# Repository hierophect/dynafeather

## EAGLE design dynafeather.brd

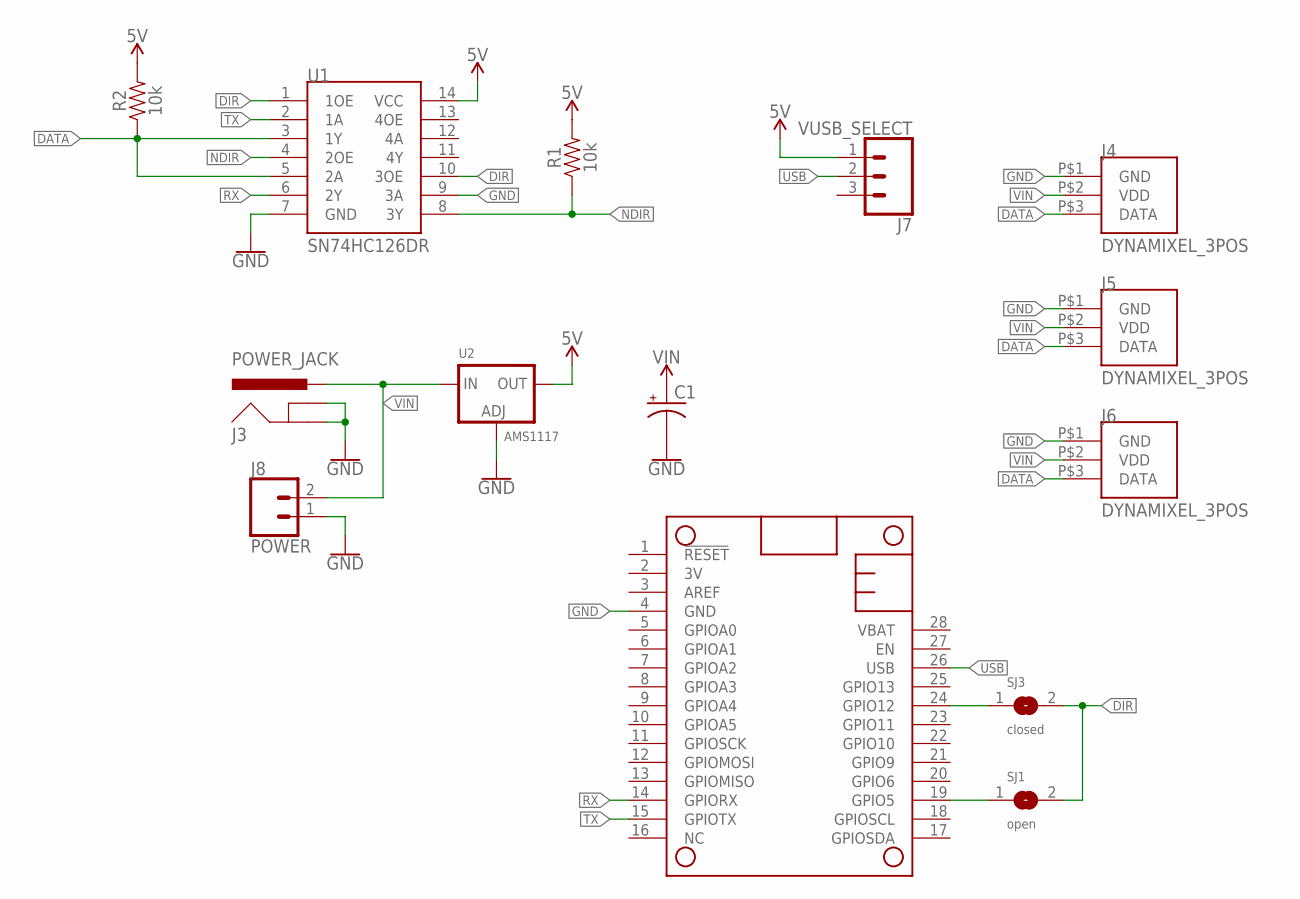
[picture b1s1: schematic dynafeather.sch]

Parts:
C1: ALUM_CAP_0605; 153CLV-0605
J3: POWER_JACK; POWER_JACK_PTH
J4, J5, J6: DYNAMIXEL_3POS; CONN-MSPOX-3POS
J7: VUSB_SELECT; 1X03_LOCK
J8: POWER; SCREWTERMINAL-3.5MM-2
MS1: FEATHERWING
R1, R2: 10k; 0603
SJ1: open; SOLDERJUMPER_REFLOW
SJ3: closed; SOLDERJUMPER_CLOSEDWIRE
U1: SN74HC126DR; SOP14
U2: AMS1117; SOT223-R

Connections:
5V: J7.1, R1.2, R2.2, U1.14 (VCC), U2.2 (OUT), U2.4 (OUT)
DATA: J4.P$3 (DATA), J5.P$3 (DATA), J6.P$3 (DATA), R2.1, U1.3 (1Y), U1.5 (2A)
DIR: SJ1.2, SJ3.2, U1.1 (1OE), U1.10 (3OE)
GND: C1.-, J3.GND, J3.GNDBREAK, J4.P$1 (GND), J5.P$1 (GND), J6.P$1 (GND), J8.1, MS1.4 (GND), U1.7 (GND), U1.9 (3A), U2.1 (ADJ)
unnamed: MS1.24 (GPIO12), SJ3.1
unnamed: MS1.19 (GPIO5), SJ1.1
NDIR: R1.1, U1.4 (2OE), U1.8 (3Y)
RX: MS1.14 (GPIORX), U1.6 (2Y)
TX: MS1.15 (GPIOTX), U1.2 (1A)
USB: J7.2, MS1.26 (USB)
VIN: C1.+, J3.PWR, J4.P$2 (VDD), J5.P$2 (VDD), J6.P$2 (VDD), J8.2, U2.3 (IN)

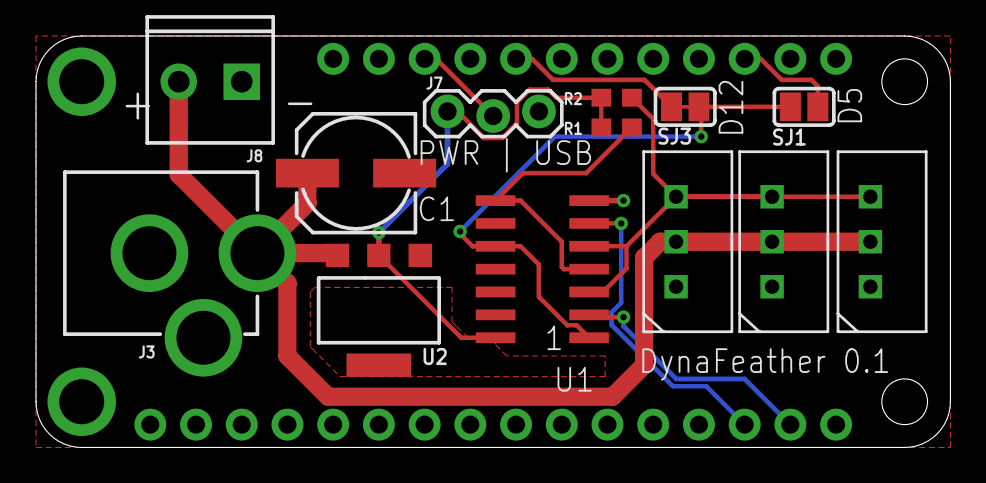
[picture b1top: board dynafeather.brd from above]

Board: 2 copper layers, 50.8 x 22.9 mm, 14 parts (0 on the bottom side), 11 nets.

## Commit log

2021-02-12 Base design

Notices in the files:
parts and their libraries:
SparkFun-Connectors: Licensing: Creative Commons ShareAlike 4.0 International - https://creativecommons.org/licenses/by-sa/4.0
microbuilder: This work is placed in the public domain, and may be freely used for commercial and non-commercial work with the following conditions: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
